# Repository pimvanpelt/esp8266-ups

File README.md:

# ESP8266 based PicoUPS Microcontroller

See [Documentation](docs/) for more details.

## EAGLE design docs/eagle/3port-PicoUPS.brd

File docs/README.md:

# Introduction

This directory contains additional documentation and thoughts about this project.
I have a bunch of 12V devices in a 19" rack at home -- largely [PC Engines](http://www.pcengines.ch/)
APU1/APU2, a cable modem, and some standalone NAS harddrives. To avoid a 
small battalion of powerbricks, one for each of these (I counted 8 of them
when I started this project), and because I find it a bit sad to use a 220V
UPS to turn a battery into 220V, just to turn it back into 12V DC again by
a powerbrick, I decided to consolidate.

## Design

I wanted to design a system that introspects the 12V power supply: input, output,
and battery. It must not be intrusive, meaning: if it doesn't work, it should
"fail open" and simply provide power to the output ports. When powered/operational,
I want to be able to switch off any given output port (briefly, not necessarily
permanently), because every now and again I botch an update/upgrade on my
APU servers, which cannot always be fixed by serial consoles. Rebooting brings
me into the BIOS, and machines are almost ~always recoverable that way.

## Hardware

For many years I've been using these little [PicoUPS](http://www.mini-box.com/picoUPS-100-12V-DC-micro-UPS-system-battery-backup-system)
devices, which take 15-18V input, connect a sealed lead acid (SLA) 12V battery,
keep that battery charged, while providing protected 15V output to a set of
devices, switching over to the battery if power fails, and switching back
to power, automatically charging the SLA, when it is available. They're
wonderful little devices:

### Requirements

Looking at what I want this system to do:

*   Sense input voltage and current on Vin
*   Sense voltage and current to/from battery on BAT
*   Determine the State of Charge of battery
*   Sense voltage on Vout
*   Have N downstream ports, each of which:
    *   Ability to cycle a port (turn off and on again)
    *   Sense current to the connected device
*   Reliability -- any Arduino / ESP8266 / Foo microcontroller should not perturb operations
*   Connectivity -- system must be on the network, scraped by Prometheus

Specifically the reliability angle is important -- some of the APU2 servers
are critical infrastucture (to me, anyway), as they hold my gateway
functionality, my Subversion server, my serial switch, and my Spongebob
Squarepants collection. I do not want the UPS to fail on me, so I've set
a requirement that no microcontroller is needed at all to operate it. The
MCU will be used only to (a) read the current/voltage values, and (b)
switch ports off, by pulling a normally-closed relais. In other words, the
UPS, if not powered at all, will work just fine, as the relais at rest
simply connects, and when pulled, disconnects the power.

### Electronics

There's a company called [ByVac](http://www.pichips.co.uk/index.php/P011_ADC)
which are not very well known, but they do happen to make a part that fits
really well with my requirements. The P012 chip is an 8-channel 10-bit ADC
which happens to have 3 outputs! It operates between 2.8V and 5.5V, so perfect
for my use case. The chip comes in two versions: **P011** is a serial speaker,
and **P012** is an I2C device. I chose the I2C speaker, because that means
the board, standalone, will be able to be connected to things like a Raspberry
Pi, or a PC Engines APU/ALIX (which I have plenty), or a dedicated MCU.

I'm a big fan of [Espressif](http://www.espressif.com/) which created the
ESP8266 (and later ESP32) microcontrollers. Those are truly marvelous parts,
as they integrate a microcontroller with dozens of GPIO pins; I2C, SPI and
UART busses; and include a fully functional 2.4GHz WiFi radio. It's really
straight forward to use these.

So the mission is to hook up one or more P012s to an ESP8266, and continuously
read the sensor data, presenting that in **/metrics** format for consumption
by [Prometheus](http://prometheus.io/), and accept some form of commands
over the network that allows an operator to turn off an output port, so that
the downstream device resets/reboots.

### Schematics / Board

You can find the schematics and the board design as eagle _.sch_ and _.brd_
files in the [eagle/](eagle/) subdirectory. You can submit the _.brd_ file
directly on http://oshpark.com/ and order it there. It'll be about USD 30,-
for three boards.

NOTE: The board/schematic is untested at this point - boards were ordered
in June 2017, and will go through testing and analysis, after which this
notice will disappear :)

### BOM

You'll need the following (modest) bill of materials to build the UPS
controller board:

*   1x board from http://oshpark.com/
*   1x P012 analog to digital converter speaking I2C, see [ByVac](http://www.pichips.co.uk/index.php/P011_ADC) website
*   D1: 1x Blue LED 0805 for PWR
*   D2,D3,D4: 3x Green LED 0805 for Output 1-3
*   R1-R7: 1K resistor 0805
*   R11,R13,R15: 3k9 resistor 0805
*   R17,R19,R21: 390R resistor 0805
*   R18,R20,R22: 10k resistor 0805
*   IC1,IC2,IC3: 3x MAX471CPA (3Amp)
*   IC4,IC5: 2x ACS712-05B (5Amp bidirectional)
*   IC6: 7805
*   C1,C2: 10 uF Tantalum 0805 capacitor
*   C3,C4: 100nF capacitor 0805
*   C5,C6: 1nF capacitor 0805
*   Q1,Q2,Q3: MMBT222A transistor
*   K1,K2,K3: Shrack V23092-A1905-A301 Relay (Type C, 5VDC)
*   J1: M04 dupont header
*   J2-J9: 5mm screw terminal connectors

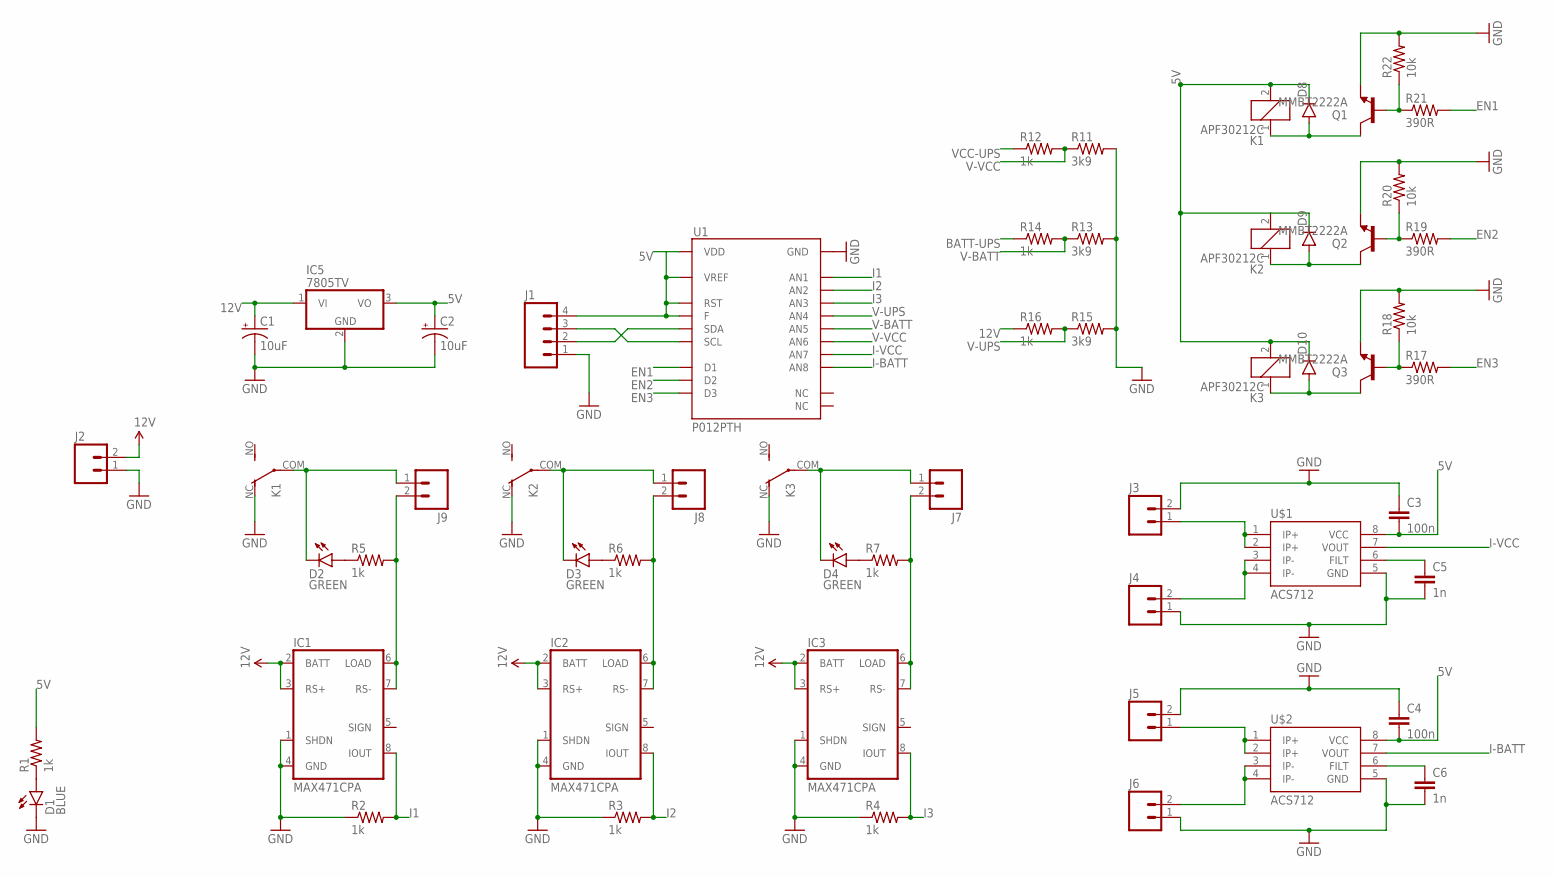
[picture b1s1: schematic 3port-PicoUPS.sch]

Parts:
C1, C2: 10uF; EIA3216
C3, C4: 100n; 0805
C5, C6: 1n; 0805
D1: BLUE; LED-0603
D2, D3, D4: GREEN; LED-0603
D8, D9, D10: DIODESOD123; SOD-123
IC1, IC2, IC3: MAX471CPA; SO08
IC5: 7805TV; TO220V
J1: M04PTH; 1X04
J2, J3, J4, J5, J6, J7, J8, J9: M025MM; SCREWTERMINAL-5MM-2
K1, K2, K3: APF30212C
Q1, Q2, Q3: MMBT2222A; SOT23-3
R1, R2, R3, R4, R5, R6, R7, R12, R14, R16: 1k; 0805
R11, R13, R15: 3k9; 0805
R17, R19, R21: 390R; 0805
R18, R20, R22: 10k; 0805
U1: P012PTH; DIL20
U$1, U$2: ACS712; SO08

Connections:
5V: C2.A (+), C3.2, C4.2, D8.C, D9.C, D10.C, IC5.3 (VO), J1.4, K1.2, K2.2, K3.2, R1.2, U1.1 (VDD), U1.4 (RST), U1.9 (F), U1.18 (VREF), U$1.8 (VCC), U$2.8 (VCC)
12V: C1.A (+), IC1.2 (BATT), IC1.3 (RS+), IC2.2 (BATT), IC2.3 (RS+), IC3.2 (BATT), IC3.3 (RS+), IC5.1 (VI), J2.2, R16.1
BATT: J5.1, U$2.1 (IP+), U$2.2 (IP+)
BATT-UPS: J6.2, R14.1, U$2.3 (IP-), U$2.4 (IP-)
EN1: R21.2, U1.2 (D1)
EN2: R19.2, U1.6 (D2)
EN3: R17.2, U1.5 (D3)
GND: C1.C (-), C2.C (-), C3.1, C4.1, C5.2, C6.2, D1.C, IC1.1 (SHDN), IC1.4 (GND), IC2.1 (SHDN), IC2.4 (GND), IC3.1 (SHDN), IC3.4 (GND), IC5.2 (GND), J1.1, J2.1, J3.2, J4.1, J5.2, J6.1, K1.NC (O), K2.NC (O), K3.NC (O), Q1.2 (E), Q2.2 (E), Q3.2 (E), R2.1, R3.1, R4.1, R11.2, R13.2, R15.2, R18.2, R20.2, R22.2, U1.20 (GND), U$1.5 (GND), U$2.5 (GND)
GND_6: D2.C, J9.1, K1.COM
GND_7: D3.C, J8.1, K2.COM
GND_8: D4.C, J7.1, K3.COM
I1: IC1.8 (IOUT), R2.2, U1.3 (AN1)
I2: IC2.8 (IOUT), R3.2, U1.7 (AN2)
I3: IC3.8 (IOUT), R4.2, U1.8 (AN3)
I-BATT: U1.19 (AN8), U$2.7 (VOUT)
I-VCC: U1.17 (AN7), U$1.7 (VOUT)
unnamed: D1.A, R1.1
unnamed: D2.A, R5.1
unnamed: D3.A, R6.1
unnamed: D4.A, R7.1
unnamed: D8.A, K1.1, Q1.3 (C)
unnamed: D9.A, K2.1, Q2.3 (C)
unnamed: D10.A, K3.1, Q3.3 (C)
unnamed: Q1.1 (B), R21.1, R22.1
unnamed: C5.1, U$1.6 (FILT)
unnamed: Q2.1 (B), R19.1, R20.1
unnamed: Q3.1 (B), R17.1, R18.1
unnamed: C6.1, U$2.6 (FILT)
OUT1: IC1.6 (LOAD), IC1.7 (RS-), J9.2, R5.2
OUT2: IC2.6 (LOAD), IC2.7 (RS-), J8.2, R6.2
OUT3: IC3.6 (LOAD), IC3.7 (RS-), J7.2, R7.2
SCL: J1.3, U1.11 (SCL)
SDA: J1.2, U1.13 (SDA)
V-BATT: R13.1, R14.2, U1.15 (AN5)
V-UPS: R15.1, R16.2, U1.14 (AN4)
V-VCC: R11.1, R12.2, U1.16 (AN6)
VCC: J3.1, U$1.1 (IP+), U$1.2 (IP+)
VCC-UPS: J4.2, R12.1, U$1.3 (IP-), U$1.4 (IP-)

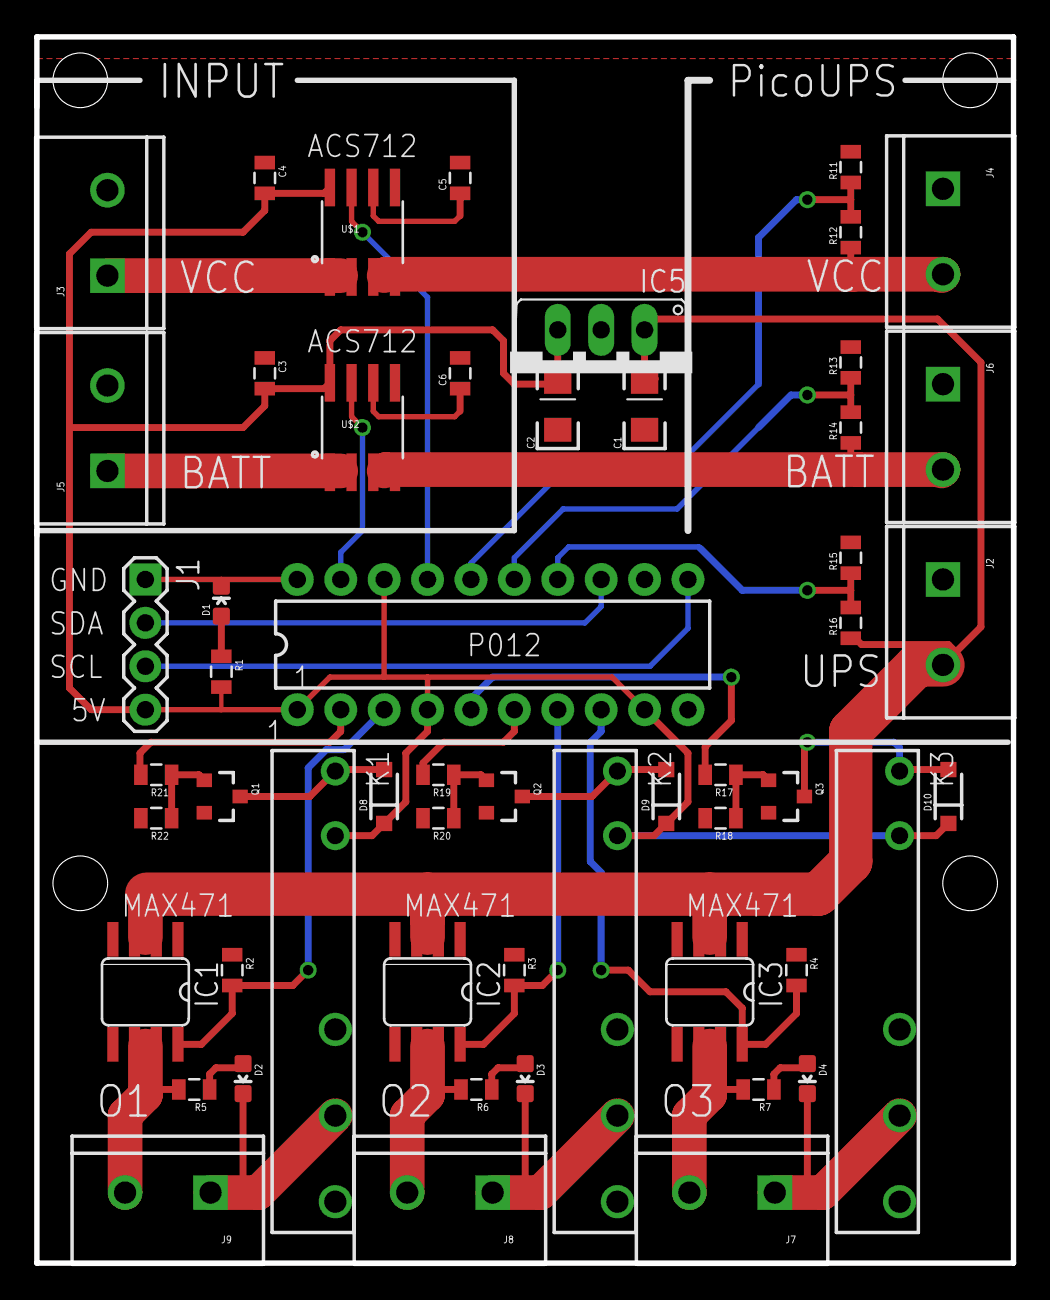
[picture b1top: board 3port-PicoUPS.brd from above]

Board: 2 copper layers, 57.2 x 71.8 mm, 54 parts (0 on the bottom side), 38 nets.

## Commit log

2017-06-20 Initial import - working demo
2017-06-20 Move sensor_timer initialization to sensor.cpp
2017-06-20 Fold p012.{cpp,h} into adcunit.{cpp,h}
2017-06-20 Move sensor_timer variable to be private to sensor.cpp
2017-06-20 Add Eagle files
2017-06-20 Add PNGs of version1 of the board design
2017-06-20 Add hardware README - just to get myself started
2017-06-20 Resize PNGs
2017-06-20 Add some more language on the design principles
2017-06-20 Add picoups picture
2017-06-20 Attribution for TimerObject original author
2017-06-20 Only reboot upon successful flash. Also, fix the error reporting if things go wrong.
2017-06-20 Point folks at the doc/ directory
2017-06-20 Fix some typos, and readability issues
2017-06-20 Fix some readability issues
2017-06-22 Introduce DEFINEs for the ADC channels - fix a bug along the way :)
2017-06-22 Set correct channel for input/battery current
2017-06-23 Rename library, because more parts will be added soon
2017-06-23 Add IRF3709Z @DPAK
2017-06-24 Replaced 7805 with SMD LM1117 - moved it up the board in preparation of adding switches on the output ports
2017-06-25 Upgraded Eagle to 8.2.2; named 'VCC' and 'BATT' signal lines
2017-06-30 Redesign the output section to include the relays and drivers.
2017-07-03 Add LM7805 in D2PAK / TO-263 package
2017-07-03 Move from 0603 to 0805 components
2017-07-03 Swap out AMS1117 for LM7805, as the former has max voltage of 15V, while we're running at 18V - LM7805 is rated to 20V
2017-07-06 Cosmetic changes - flip the direction of R20 (to be the same as R18/R22); also straighten the VBATT and VIN traces on the righthand side J4 and J6; also move the labels 'MAX471' up a bit so they are 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
2017-07-09 Replace potis with fixed voltage dividers at 3k9 : 1k each which will give me 24.5V of range. 15V input will now read 3.061V on the ADC inputs.
2017-07-09 New pictures of Version 1.4
2017-07-09 Update BOM to v1.4 materials
2017-08-01 Introduce ADCUnit::Initialize() and call it always. This ensures the P012 is in VREF and 5ms sampling mode. Add ADCUnit::SetAddress() to change the I2C address of a P012.
    Remove sensor_output() as it was for testing only, and the relays work :)
2017-08-03 Add PDF of the schematic so folks don't have to run Eagle to see it.

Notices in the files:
parts and their libraries:
SparkFun-LED: Licensing: Creative Commons ShareAlike 4.0 International - https://creativecommons.org/licenses/by-sa/4.0
